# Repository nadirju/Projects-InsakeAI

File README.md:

# Projects-InsakeAI
This repository contains the PCB Design Projects I have completed in InstakeAI.

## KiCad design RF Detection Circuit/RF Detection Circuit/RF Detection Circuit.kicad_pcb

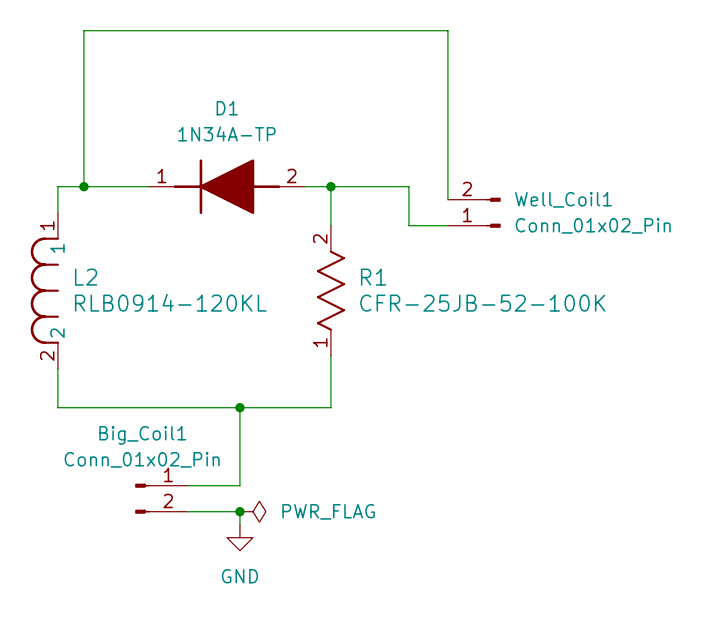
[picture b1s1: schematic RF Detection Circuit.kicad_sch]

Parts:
Big_Coil1: Conn_01x02_Pin; PinHeader_1x02_P2.54mm_Vertical
D1: 1N34A-TP; DIOAD1850W56L762D272; Mouser Part Number 833-1N34A-TP
L2: RLB0914-120KL; IND_BOURNS_RLB0914
R1: CFR-25JB-52-100K; YAG_CFR25_YAG
Well_Coil1: Conn_01x02_Pin; PinHeader_1x02_P2.54mm_Vertical

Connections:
GND: Big_Coil1.2
unnamed: Big_Coil1.1, L2.2, R1.1
unnamed: D1.2 (A), R1.2, Well_Coil1.1
unnamed: D1.1 (K), L2.1, Well_Coil1.2

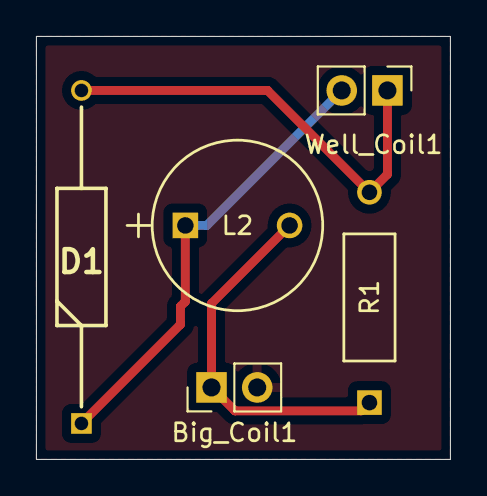
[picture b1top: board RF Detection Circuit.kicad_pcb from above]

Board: 2 copper layers, 23.0 x 23.5 mm, 5 parts (0 on the bottom side), 3 nets.

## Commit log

2025-07-01 Add files via upload
    PDM Project is added.
2025-07-01 Rename Reference for SCL and SDA.png to Reference for I2C.png
2025-07-01 Add files via upload
    RF Detection Circuit project is located in this directory.
